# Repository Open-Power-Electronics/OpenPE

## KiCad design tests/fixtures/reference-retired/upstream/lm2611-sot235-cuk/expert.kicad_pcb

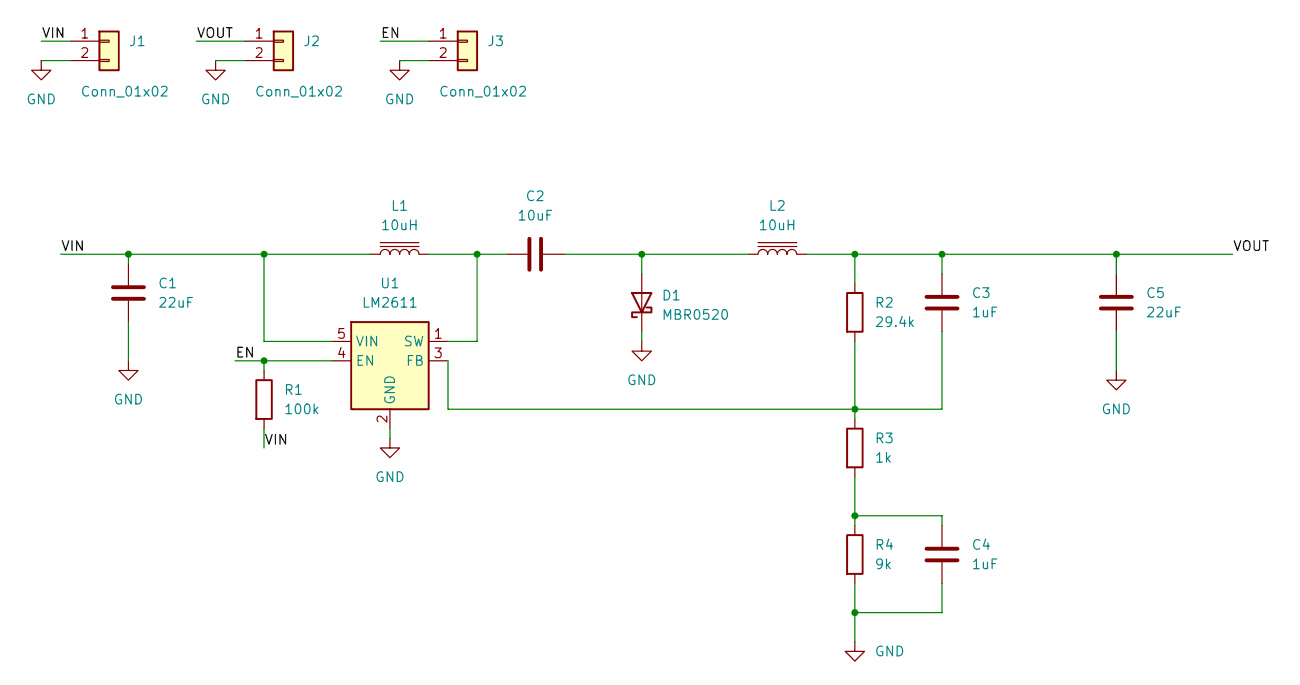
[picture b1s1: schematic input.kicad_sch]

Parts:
C1, C5: 22uF; C_1210_3225Metric
C2: 10uF; C_0603_1608Metric
C3, C4: 1uF; C_0603_1608Metric
D1: MBR0520; D_SOD-123
J1, J2: Conn_01x02; Molex_KK-254_AE-6410-02A_1x02_P2.54mm_Vertical
J3: Conn_01x02; PinHeader_1x02_P1.00mm_Vertical
L1, L2: 10uH; L_Changjiang_FNR6028S
R1: 100k; R_0805_2012Metric
R2: 29.4k; R_0805_2012Metric
R3: 1k; R_0805_2012Metric
R4: 9k; R_0805_2012Metric
U1: LM2611; SOT-23-5

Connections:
/EN: J3.1, R1.1, U1.4 (EN)
/VIN: C1.1, J1.1, L1.1, R1.2, U1.5 (VIN)
/VOUT: C3.2, C5.1, J2.1, L2.2, R2.1
GND: C1.2, C4.1, C5.2, D1.1 (K), J1.2, J2.2, J3.2, R4.2, U1.2 (GND)
unnamed: C4.2, R3.2, R4.1
unnamed: C2.1, D1.2 (A), L2.1
unnamed: C3.1, R2.2, R3.1, U1.3 (FB)
unnamed: C2.2, L1.2, U1.1 (SW)

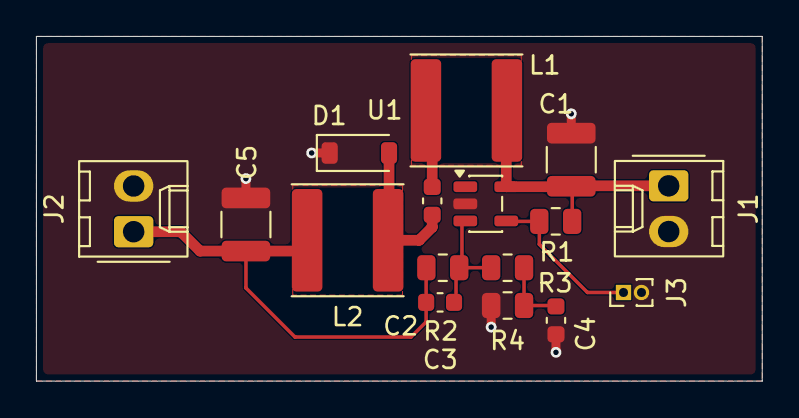
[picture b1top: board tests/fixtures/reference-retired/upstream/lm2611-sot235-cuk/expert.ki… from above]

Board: 2 copper layers, 40.3 x 19.1 mm, 16 parts (0 on the bottom side), 8 nets.

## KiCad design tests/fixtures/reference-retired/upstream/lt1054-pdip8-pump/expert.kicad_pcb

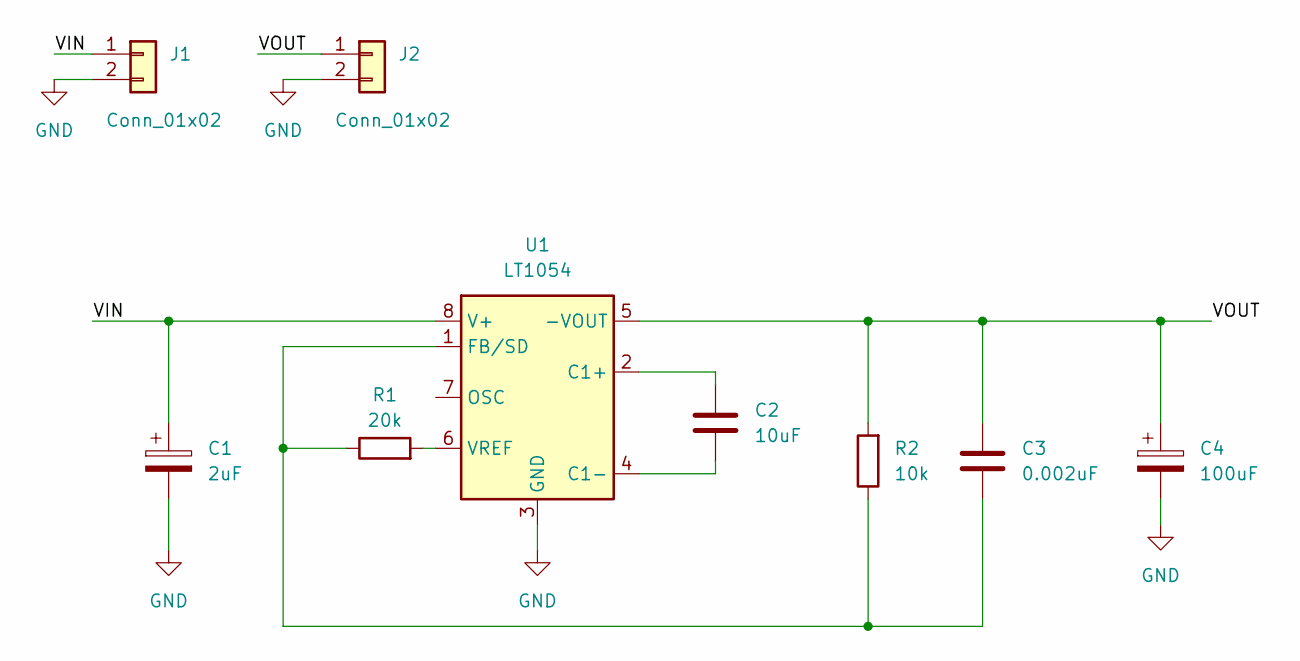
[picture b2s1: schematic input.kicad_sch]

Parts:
C1: 2uF; CP_Radial_D6.3mm_P2.50mm
C2: 10uF; C_1210_3225Metric
C3: 0.002uF; C_1210_3225Metric
C4: 100uF; CP_Radial_D6.3mm_P2.50mm
J1, J2: Conn_01x02; JST_PH_B2B-PH-K_1x02_P2.00mm_Vertical
R1: 20k; R_1206_3216Metric
R2: 10k; R_1206_3216Metric
U1: LT1054; DIP-8_W7.62mm

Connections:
/VIN: C1.1, J1.1, U1.8 (V+)
/VOUT: C3.1, C4.1, J2.1, R2.2, U1.5 (-VOUT)
GND: C1.2, C4.2, J1.2, J2.2, U1.3 (GND)
unnamed: C2.1, U1.2 (C1+)
unnamed: C2.2, U1.4 (C1-)
unnamed: C3.2, R1.1, R2.1, U1.1 (FB/SD)
unnamed: R1.2, U1.6 (VREF)

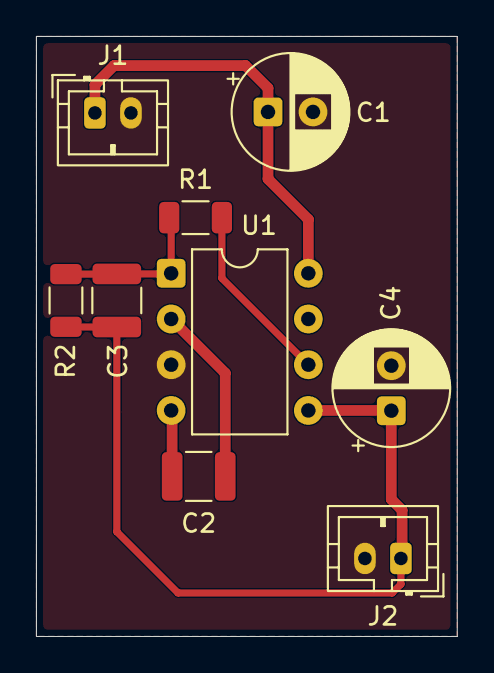
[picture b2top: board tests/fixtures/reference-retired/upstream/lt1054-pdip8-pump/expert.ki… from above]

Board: 2 copper layers, 23.4 x 33.3 mm, 9 parts (0 on the bottom side), 7 nets.

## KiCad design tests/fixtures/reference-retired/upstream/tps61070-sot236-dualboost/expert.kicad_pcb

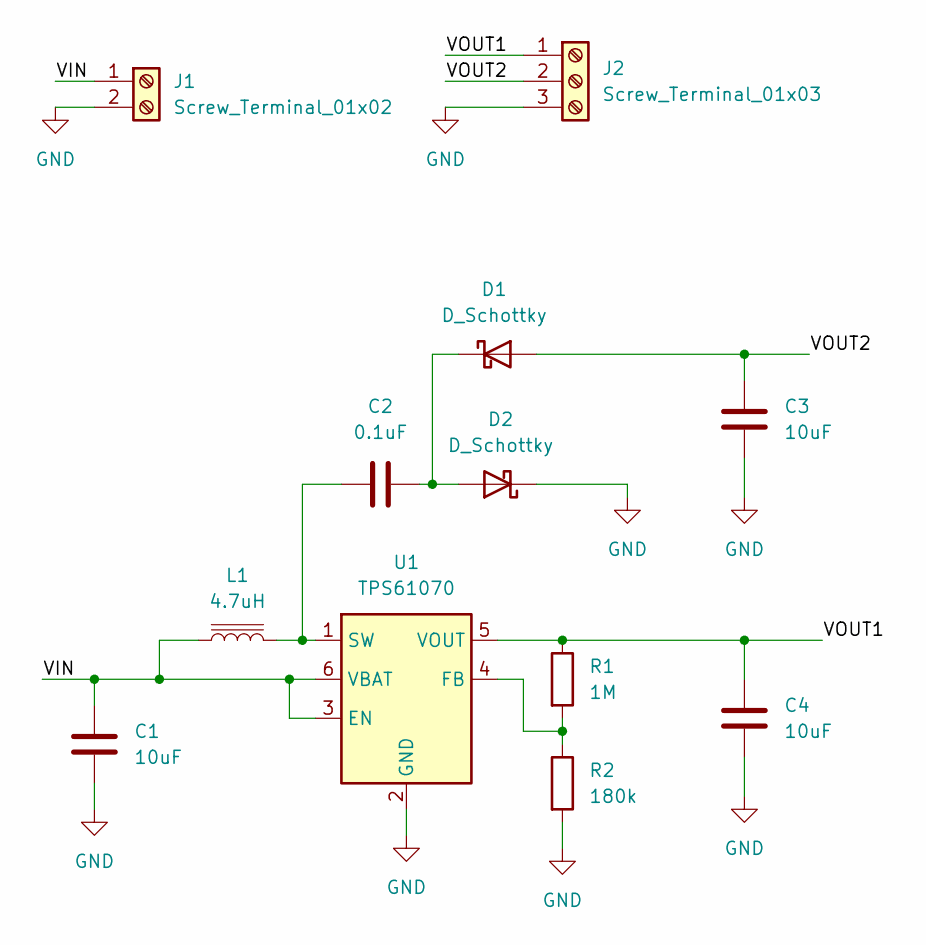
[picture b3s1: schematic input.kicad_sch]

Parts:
C1, C3, C4: 10uF; C_0805_2012Metric
C2: 0.1uF; C_0805_2012Metric
D1, D2: D_Schottky; D_SOD-123
J1: Screw_Terminal_01x02; TerminalBlock_Phoenix_MPT-0,5-2-2.54_1x02_P2.54mm_Horizontal
J2: Screw_Terminal_01x03; TerminalBlock_Phoenix_MPT-0,5-3-2.54_1x03_P2.54mm_Horizontal
L1: 4.7uH; L_APV_ANR4010
R1: 1M; R_0603_1608Metric
R2: 180k; R_0603_1608Metric
U1: TPS61070; SOT-23-6

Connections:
/VIN: C1.1, J1.1, L1.1, U1.3 (EN), U1.6 (VBAT)
/VOUT1: C4.1, J2.1, R1.1, U1.5 (VOUT)
/VOUT2: C3.2, D1.2 (A), J2.2
GND: C1.2, C3.1, C4.2, D2.1 (K), J1.2, J2.3, R2.2, U1.2 (GND)
unnamed: C2.1, D1.1 (K), D2.2 (A)
unnamed: R1.2, R2.1, U1.4 (FB)
unnamed: C2.2, L1.2, U1.1 (SW)

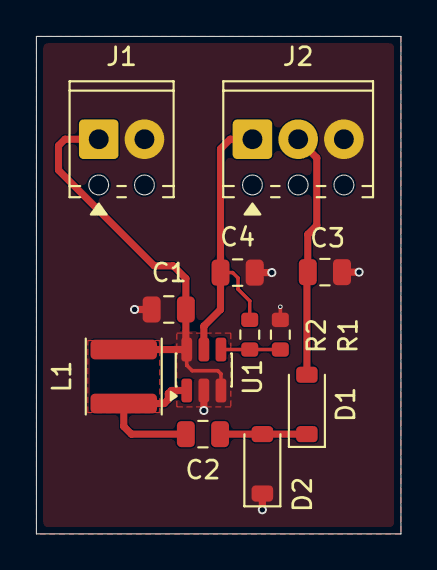
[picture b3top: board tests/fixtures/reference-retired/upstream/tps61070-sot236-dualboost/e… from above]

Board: 2 copper layers, 20.2 x 27.6 mm, 12 parts (0 on the bottom side), 7 nets.

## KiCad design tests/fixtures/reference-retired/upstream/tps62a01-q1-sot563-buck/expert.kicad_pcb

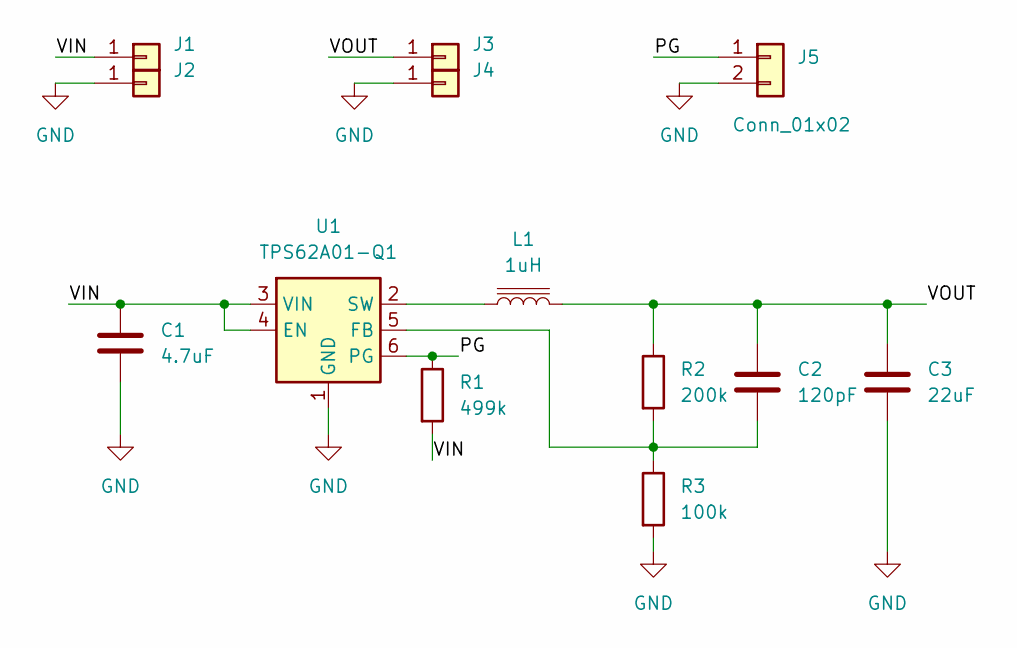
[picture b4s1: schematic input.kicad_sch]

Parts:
C1: 4.7uF; C_0805_2012Metric
C2: 120pF; C_0603_1608Metric
C3: 22uF; C_0805_2012Metric
J1, J2, J3, J4: Conn_01x01; SolderWire-0.5sqmm_1x01_D0.9mm_OD2.3mm
J5: Conn_01x02; PinHeader_1x02_P1.27mm_Vertical
L1: 1uH; L_Wurth_WE-LQSH-2512
R1: 499k; R_0603_1608Metric
R2: 200k; R_0603_1608Metric
R3: 100k; R_0603_1608Metric
U1: TPS62A01-Q1; SOT-563

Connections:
/PG: J5.1, R1.1, U1.6 (PG)
/VIN: C1.1, J1.1 (Pin_1_1), R1.2, U1.3 (VIN), U1.4 (EN)
/VOUT: C2.1, C3.1, J3.1 (Pin_1_1), L1.2, R2.1
GND: C1.2, C3.2, J2.1 (Pin_1_1), J4.1 (Pin_1_1), J5.2, R3.2, U1.1 (GND)
unnamed: C2.2, R2.2, R3.1, U1.5 (FB)
unnamed: L1.1, U1.2 (SW)

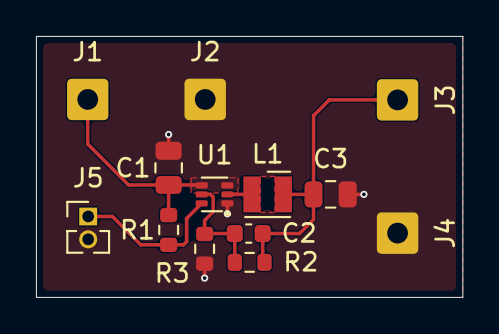
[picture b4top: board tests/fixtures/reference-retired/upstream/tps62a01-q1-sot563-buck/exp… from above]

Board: 2 copper layers, 23.7 x 14.5 mm, 13 parts (0 on the bottom side), 6 nets.

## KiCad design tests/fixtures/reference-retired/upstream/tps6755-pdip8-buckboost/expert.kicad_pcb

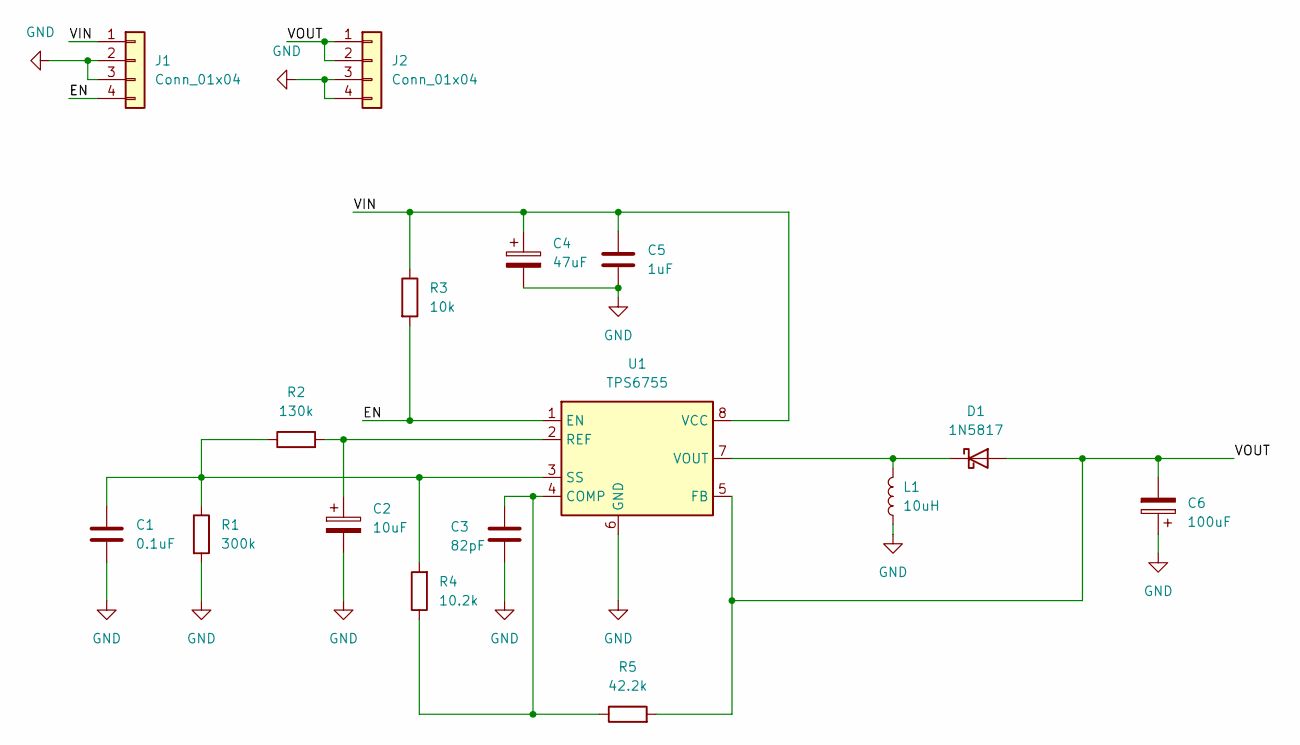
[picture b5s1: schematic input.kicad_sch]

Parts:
C1: 0.1uF; C_0805_2012Metric
C2: 10uF; CP_EIA-3528-12_Kemet-T
C3: 82pF; C_0805_2012Metric
C4: 47uF; CP_EIA-7343-20_Kemet-V
C5: 1uF; C_1206_3216Metric
C6: 100uF; CP_EIA-7343-20_Kemet-V
D1: 1N5817; D_DO-41_SOD81_P10.16mm_Horizontal
J1, J2: Conn_01x04; JST_PH_S4B-PH-K_1x04_P2.00mm_Horizontal
L1: 10uH; L_Changjiang_FXL0640
R1: 300k; R_0805_2012Metric
R2: 130k; R_0805_2012Metric
R3: 10k; R_0805_2012Metric
R4: 10.2k; R_0805_2012Metric
R5: 42.2k; R_0805_2012Metric
U1: TPS6755; DIP-8_W7.62mm

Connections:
/EN: J1.4, R3.2, U1.1 (EN)
/VIN: C4.1, C5.1, J1.1, R3.1, U1.8 (VCC)
/VOUT: C6.2, D1.2 (A), J2.1, J2.2, R5.2, U1.5 (FB)
GND: C1.2, C2.2, C3.2, C4.2, C5.2, C6.1, J1.2, J1.3, J2.3, J2.4, L1.1, R1.2, U1.6 (GND)
unnamed: D1.1 (K), L1.2, U1.7 (VOUT)
unnamed: C3.1, R4.1, R5.1, U1.4 (COMP)
unnamed: C2.1, R2.2, U1.2 (REF)
unnamed: C1.1, R1.1, R2.1, R4.2, U1.3 (SS)

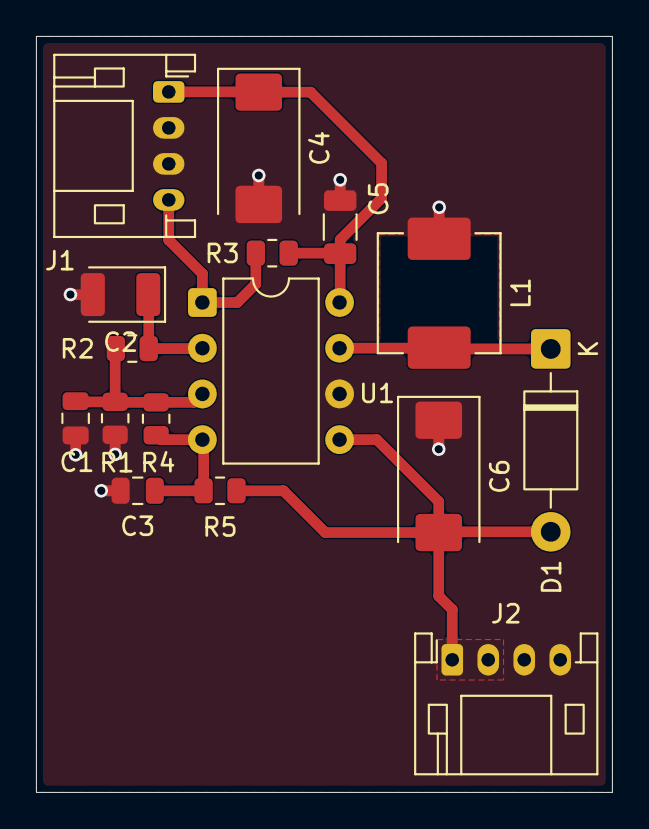
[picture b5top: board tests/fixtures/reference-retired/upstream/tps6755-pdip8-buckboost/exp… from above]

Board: 2 copper layers, 32.0 x 42.0 mm, 16 parts (0 on the bottom side), 8 nets.
